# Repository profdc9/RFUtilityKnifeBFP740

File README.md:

This is a pack of RF circuits all laid out onto the same PCB.  They use the X-band transistor BFP740 with 44 GHz transition frequency.  There are five circuits: an Active RF probe, a Active RF Differential Probe, series and shunt noises generator, a Gilbert cell mixer, and a RF amplifier.

These designs are by D. Marks KW4TI and are distributed under the Creative Commons Shared Alike Attribution (CC-BY-SA 4.0) license.

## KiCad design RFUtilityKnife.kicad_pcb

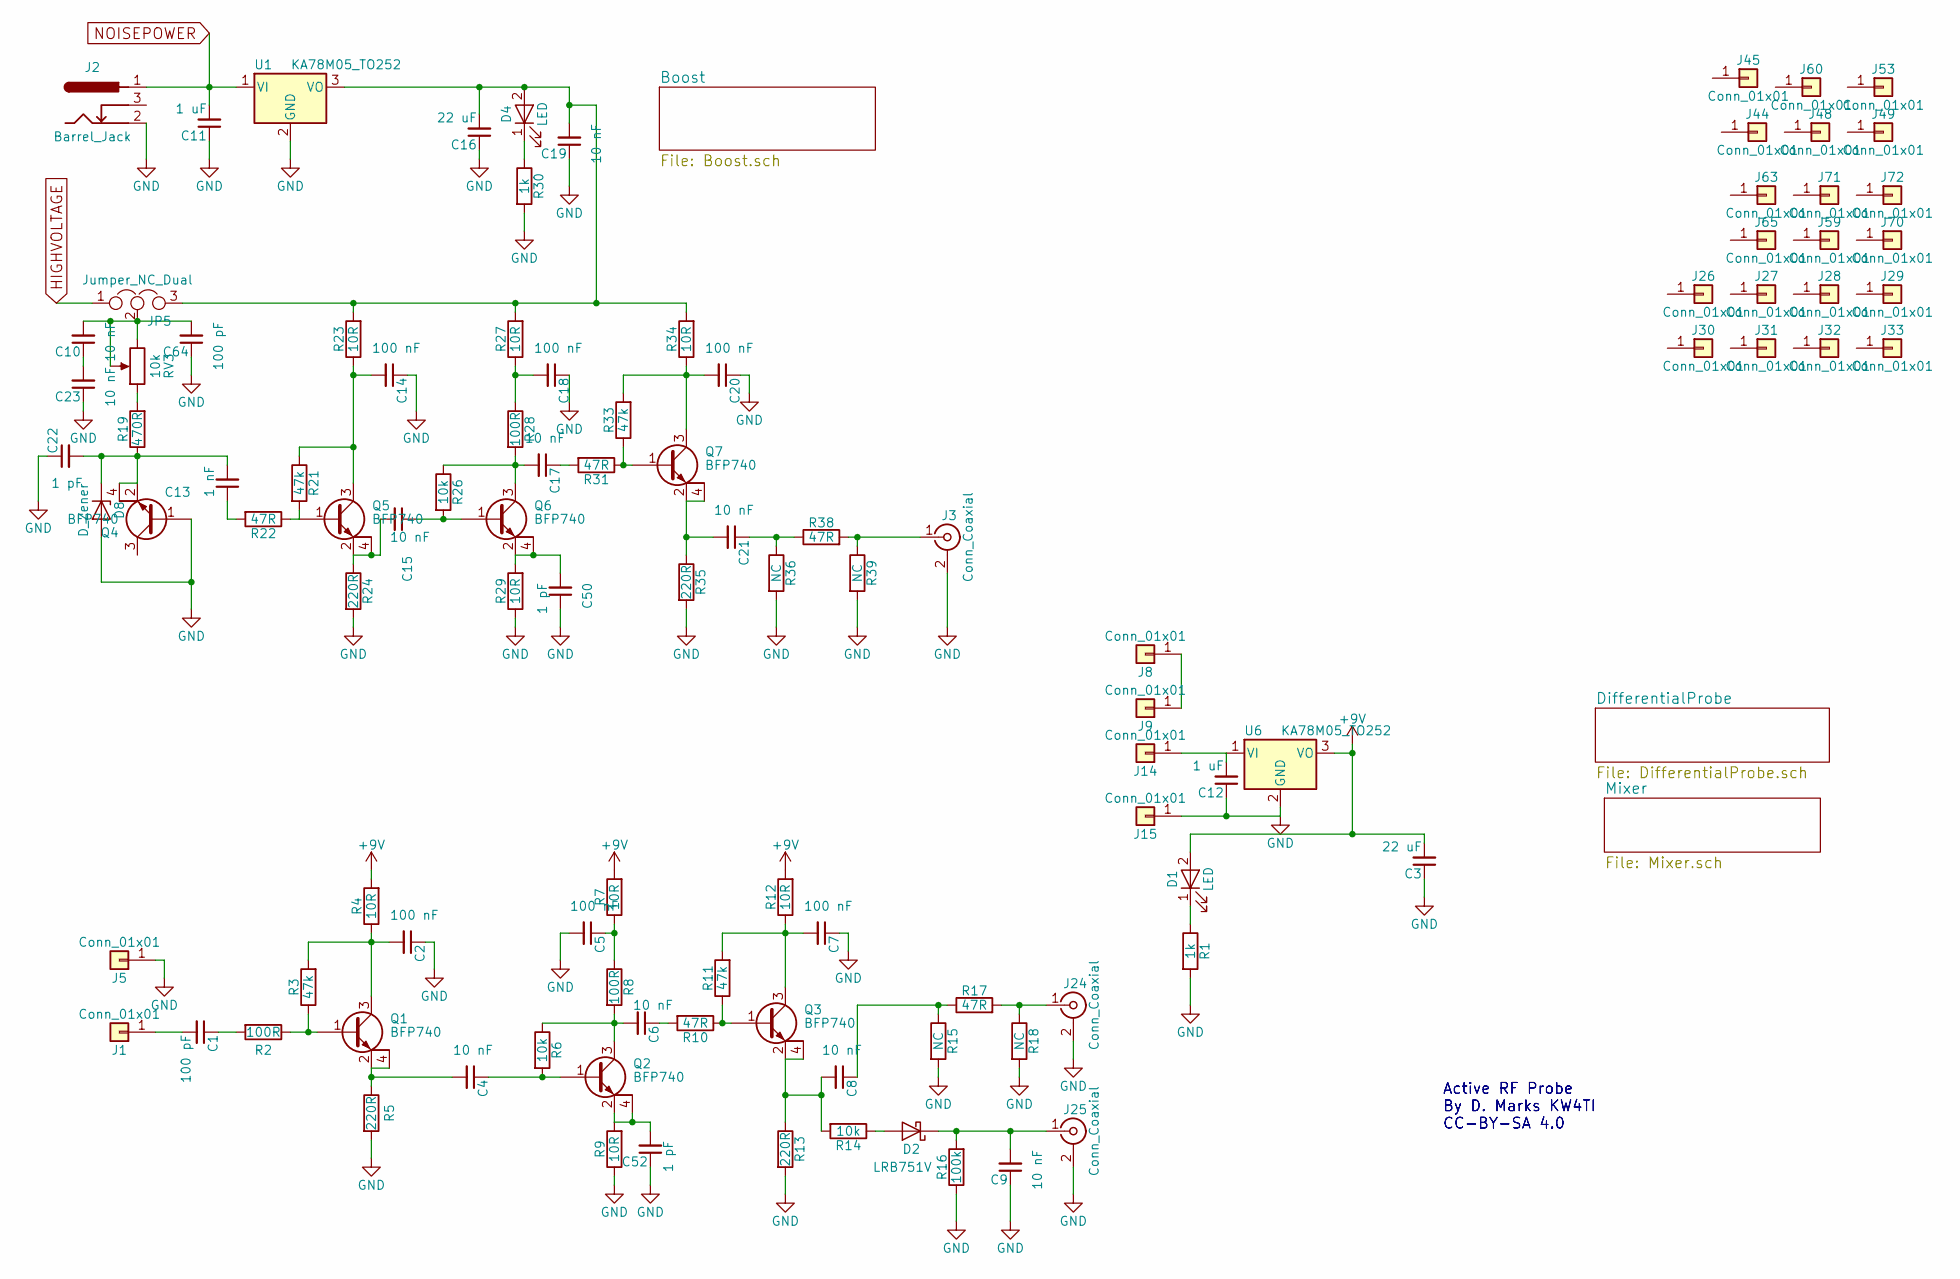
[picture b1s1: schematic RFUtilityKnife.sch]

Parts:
C1: 100 pF; C_0402_NoSilk; LCSC C1546
C2, C5, C7, C14, C18, C20: 100 nF; C_0402_NoSilk; LCSC C1525
C3, C16: 22 uF; C_0805_HandSoldering; LCSC C45783
C4, C6, C8, C15, C17, C21: 10 nF; C_0402_NoSilk; LCSC C15195
C9, C10, C19, C23: 10 nF; C_0805_HandSoldering; LCSC C1710
C11, C12: 1 uF; C_0805_HandSoldering; LCSC C28323
C13: 1 nF; C_0402_NoSilk; LCSC C1523
C22, C50, C52: 1 pF; C_0402_NoSilk; LCSC C14971
C64: 100 pF; C_0805_HandSoldering; LCSC C1790
D1, D4: LED; LED_0805_HandSoldering; LCSC C2296
D2: LRB751V; D_SOD-323_HandSoldering; LCSC C131730
D8: D_Zener; D_MiniMELF
J1, J5, J8, J9, J14, J15: Conn_01x01; PadHole
J2: Barrel_Jack; BARREL_JACK
J3, J24, J25: Conn_Coaxial; Amphenol_RF_SMA_132289
J26, J27, J28, J29, J30, J31, J32, J33, J44, J45, J48, J49, J53, J59, J60, J63, J65, J70, J71, J72: Conn_01x01; BigSlot
JP5: Jumper_NC_Dual; Pin_Header_Straight_1x03_Pitch2.54mm
Q1, Q2, Q3, Q4, Q5, Q6, Q7: BFP740; SOT-343_SC-70-4_Handsoldering
R1, R30: 1k; R_0805_HandSoldering; LCSC C17513
R2, R8, R28: 100R; R_0402_NoSilk; LCSC C25076
R3, R11, R21, R33: 47k; R_0402_NoSilk; LCSC C25792
R4, R7, R9, R12, R23, R27, R29, R34: 10R; R_0402_NoSilk; LCSC C25077
R5, R13, R24, R35: 220R; R_0402_NoSilk; LCSC C25091
R6, R14, R26: 10k; R_0402_NoSilk; LCSC C25744
R10, R17, R22, R31, R38: 47R; R_0402_NoSilk; LCSC C25118
R15, R18, R36, R39: NC; R_0402_NoSilk
R16: 100k; R_0402_NoSilk; LCSC C25741
R19: 470R; R_0402_NoSilk; LCSC C25117
RV3: 10k; Potentiometer_Triwood_RM-065
U1, U6: KA78M05_TO252; TO-252-3_TabPin2; LCSC C58069

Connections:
+9V: C3.2, D1.2 (A), R4.2, R7.2, R12.2, U6.3 (VO)
GND: C2.1, C3.1, C5.2, C7.1, C9.1, C11.1, C12.1, C14.1, C16.1, C18.1, C19.1, C20.1, C22.1, C23.1, C50.1, C52.1, C64.1, D8.2 (A), J2.2, J3.2 (Ext), J5.1, J15.1, J24.2 (Ext), J25.2 (Ext), Q4.1 (B), R1.2, R5.2, R9.1, R13.2, R15.2, R16.1, R18.2, R24.2, R29.1, R30.2, R35.2, R36.2, R39.2, U1.2 (GND), U6.2 (GND); also elsewhere on the board
HIGHVOLTAGE: JP5.1; also elsewhere on the board
NOISEPOWER: C11.2, J2.1, U1.1 (VI); also elsewhere on the board
unnamed: C1.1, R2.2
unnamed: C1.2, J1.1
unnamed: C2.2, Q1.3 (C), R3.2, R4.1
unnamed: C4.1, Q2.1 (B), R6.2
unnamed: C4.2, Q1.2 (E), Q1.4 (E2), R5.1
unnamed: C5.1, R7.1, R8.1
unnamed: C6.1, R10.2
unnamed: C6.2, Q2.3 (C), R6.1, R8.2
unnamed: C7.2, Q3.3 (C), R11.2, R12.1
unnamed: C8.1, R15.1, R17.1
unnamed: C8.2, Q3.2 (E), Q3.4 (E2), R13.1, R14.2
unnamed: C9.2, D2.1 (K), J25.1 (In), R16.2
unnamed: C10.1, C23.2
unnamed: C10.2, C64.2, JP5.2, RV3.2, RV3.3
unnamed: C12.2, J14.1, U6.1 (VI)
unnamed: C13.1, R22.2
unnamed: C13.2, C22.2, D8.1 (K), Q4.2 (E), Q4.4 (E2), R19.1
unnamed: C14.2, Q5.3 (C), R21.1, R23.1
unnamed: C15.1, Q6.1 (B), R26.2
unnamed: C15.2, Q5.2 (E), Q5.4 (E2), R24.1
unnamed: C16.2, C19.2, D4.2 (A), JP5.3, R23.2, R27.2, R34.2, U1.3 (VO)
unnamed: C17.1, R31.2
unnamed: C17.2, Q6.3 (C), R26.1, R28.2
unnamed: C18.2, R27.1, R28.1
unnamed: C20.2, Q7.3 (C), R33.2, R34.1
unnamed: C21.1, R36.1, R38.1
unnamed: C21.2, Q7.2 (E), Q7.4 (E2), R35.1
unnamed: C50.2, Q6.2 (E), Q6.4 (E2), R29.2
unnamed: C52.2, Q2.2 (E), Q2.4 (E2), R9.2
unnamed: D1.1 (K), R1.1
unnamed: D2.2 (A), R14.1
unnamed: D4.1 (K), R30.1
unnamed: J3.1 (In), R38.2, R39.1
unnamed: J8.1, J9.1
unnamed: J24.1 (In), R17.2, R18.1
unnamed: Q1.1 (B), R2.1, R3.1
unnamed: Q3.1 (B), R10.1, R11.1
unnamed: Q5.1 (B), R21.2, R22.1
unnamed: Q7.1 (B), R31.1, R33.1
unnamed: R19.2, RV3.1

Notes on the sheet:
Active RF Probe By D. Marks KW4TI CC-BY-SA 4.0

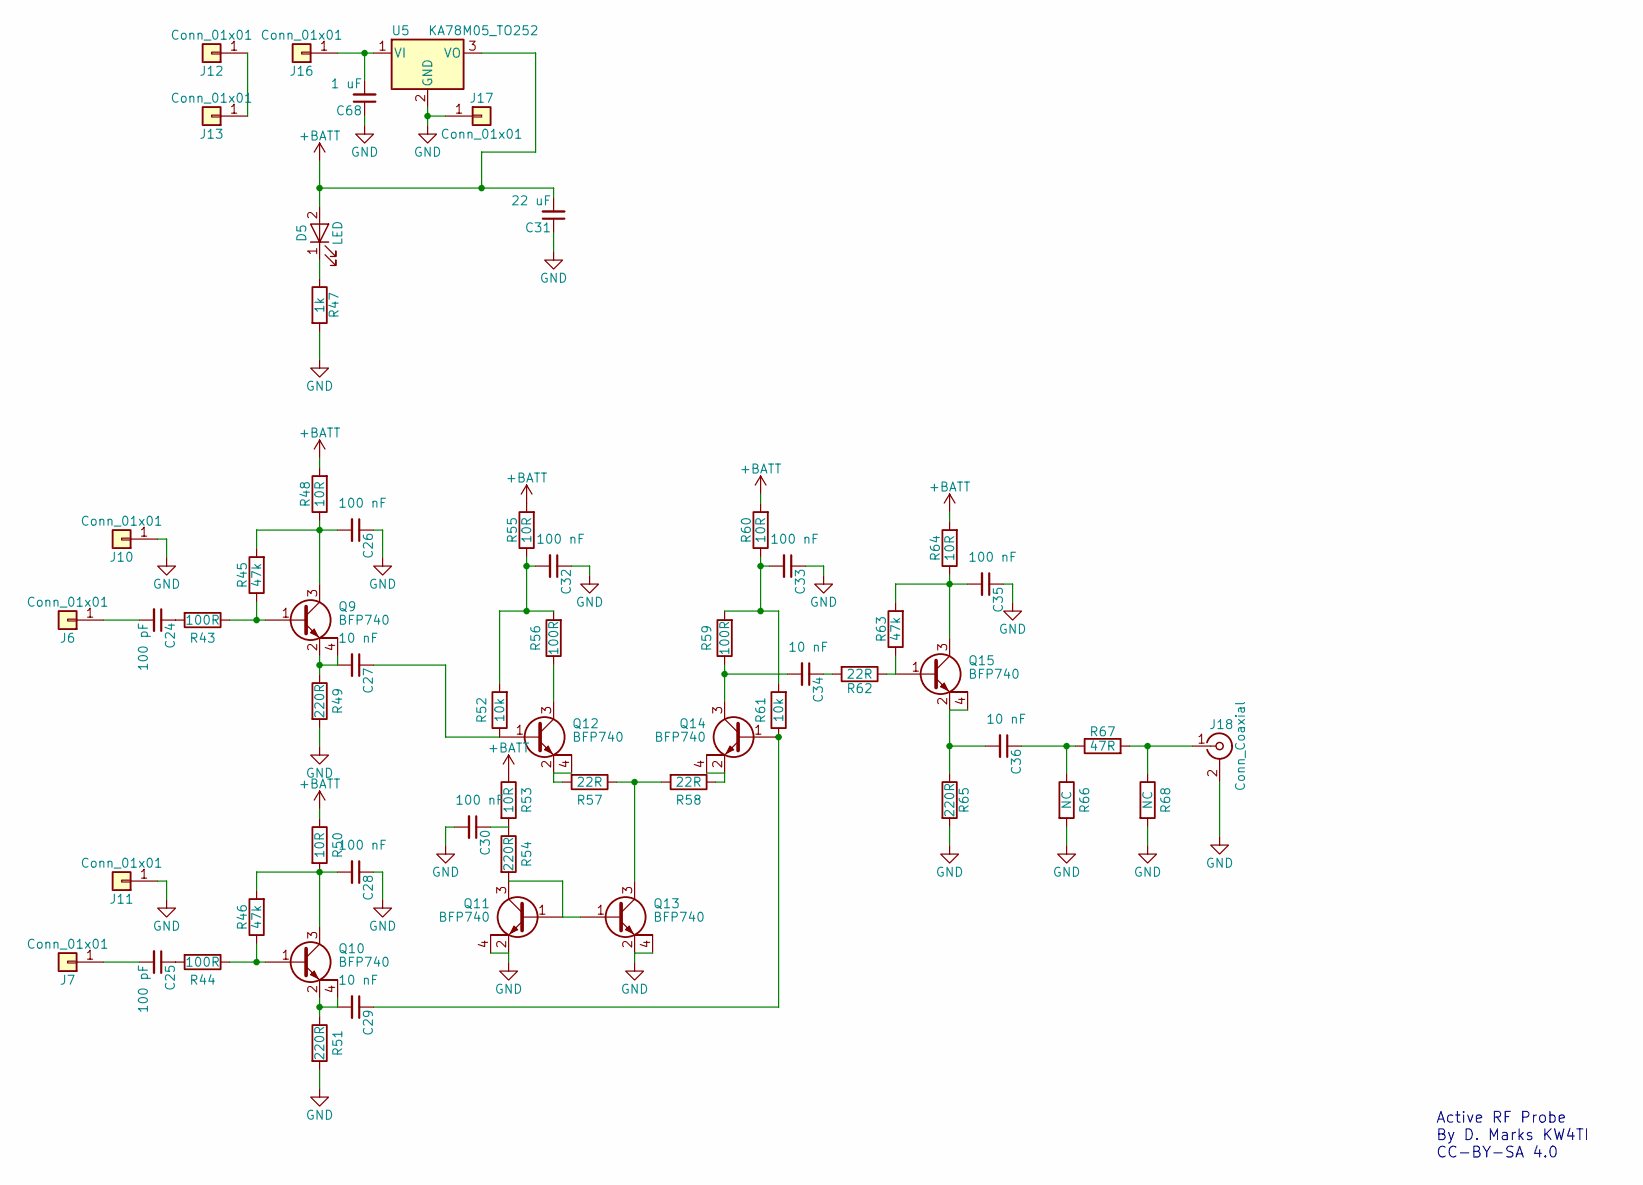
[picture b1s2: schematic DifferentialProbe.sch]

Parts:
C24, C25: 100 pF; C_0402_NoSilk; LCSC C1546
C26, C28, C30, C32, C33, C35: 100 nF; C_0402_NoSilk; LCSC C1525
C27, C29, C34, C36: 10 nF; C_0402_NoSilk; LCSC C15195
C31: 22 uF; C_0805_HandSoldering; LCSC C45783
C68: 1 uF; C_0805_HandSoldering; LCSC C28323
D5: LED; LED_0805_HandSoldering; LCSC C2296
J6, J7, J10, J11, J12, J13, J16, J17: Conn_01x01; PadHole
J18: Conn_Coaxial; Amphenol_RF_SMA_132289
Q9, Q10, Q11, Q12, Q13, Q14, Q15: BFP740; SOT-343_SC-70-4_Handsoldering
R43, R44, R56, R59: 100R; R_0402_NoSilk; LCSC C25076
R45, R46, R63: 47k; R_0402_NoSilk; LCSC C25792
R47: 1k; R_0805_HandSoldering; LCSC C17513
R48, R50, R53, R55, R60, R64: 10R; R_0402_NoSilk; LCSC C25077
R49, R51, R54, R65: 220R; R_0402_NoSilk; LCSC C25091
R52, R61: 10k; R_0402_NoSilk; LCSC C25744
R57, R58, R62: 22R; R_0402_NoSilk; LCSC C25092
R66, R68: NC; R_0402_NoSilk
R67: 47R; R_0402_NoSilk; LCSC C25118
U5: KA78M05_TO252; TO-252-3_TabPin2; LCSC C58069

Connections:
+BATT: C31.2, D5.2 (A), R48.2, R50.1, R53.1, R55.2, R60.2, R64.2, U5.3 (VO)
GND: C26.1, C28.1, C30.2, C31.1, C32.1, C33.1, C35.1, C68.1, J10.1, J11.1, J17.1, J18.2 (Ext), Q11.2 (E), Q11.4 (E2), Q13.2 (E), Q13.4 (E2), R47.2, R49.2, R51.2, R65.2, R66.2, R68.2, U5.2 (GND); also elsewhere on the board
unnamed: C24.1, R43.2
unnamed: C24.2, J6.1
unnamed: C25.1, R44.2
unnamed: C25.2, J7.1
unnamed: C26.2, Q9.3 (C), R45.2, R48.1
unnamed: C27.1, Q12.1 (B), R52.1
unnamed: C27.2, Q9.2 (E), Q9.4 (E2), R49.1
unnamed: C28.2, Q10.3 (C), R46.2, R50.2
unnamed: C29.1, Q14.1 (B), R61.1
unnamed: C29.2, Q10.2 (E), Q10.4 (E2), R51.1
unnamed: C30.1, R53.2, R54.1
unnamed: C32.2, R52.2, R55.1, R56.2
unnamed: C33.2, R59.2, R60.1, R61.2
unnamed: C34.1, R62.2
unnamed: C34.2, Q14.3 (C), R59.1
unnamed: C35.2, Q15.3 (C), R63.2, R64.1
unnamed: C36.1, R66.1, R67.1
unnamed: C36.2, Q15.2 (E), Q15.4 (E2), R65.1
unnamed: C68.2, J16.1, U5.1 (VI)
unnamed: D5.1 (K), R47.1
unnamed: J12.1, J13.1
unnamed: J18.1 (In), R67.2, R68.1
unnamed: Q9.1 (B), R43.1, R45.1
unnamed: Q10.1 (B), R44.1, R46.1
unnamed: Q11.1 (B), Q11.3 (C), Q13.1 (B), R54.2
unnamed: Q12.2 (E), Q12.4 (E2), R57.2
unnamed: Q12.3 (C), R56.1
unnamed: Q13.3 (C), R57.1, R58.2
unnamed: Q14.2 (E), Q14.4 (E2), R58.1
unnamed: Q15.1 (B), R62.1, R63.1

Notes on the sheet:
Active RF Probe By D. Marks KW4TI CC-BY-SA 4.0

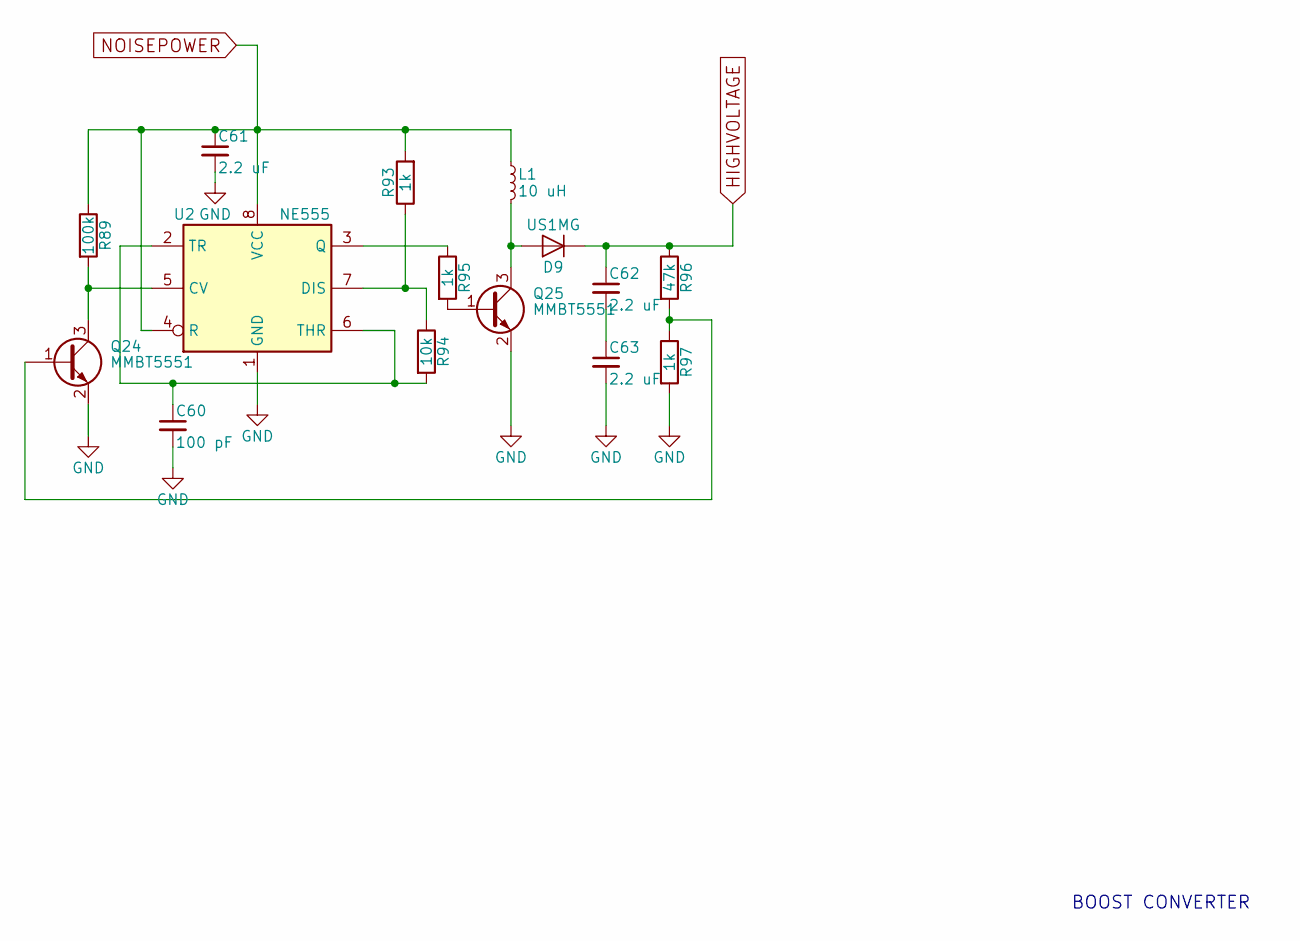
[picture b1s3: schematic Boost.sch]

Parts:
C60: 100 pF; C_0805_HandSoldering; LCSC C1790
C61, C62, C63: 2.2 uF; C_0805_HandSoldering; LCSC C49217
D9: US1MG; D_SMA_Handsoldering; LCSC C412437
L1: 10 uH; L_7.3x7.3_H4.5
Q24, Q25: MMBT5551; SOT-23; LCSC C2145
R89: 100k; R_0805_HandSoldering; LCSC C17407
R93, R95, R97: 1k; R_0805_HandSoldering; LCSC C17513
R94: 10k; R_0805_HandSoldering; LCSC C17414
R96: 47k; R_0805_HandSoldering; LCSC C17713
U2: NE555; SOIC-8_3.9x4.9mm_Pitch1.27mm; LCSC C7593

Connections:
GND: C60.2, C61.2, C63.2, Q24.2 (E), Q25.2 (E), R97.2, U2.1 (GND); also elsewhere on the board
HIGHVOLTAGE: C62.1, D9.1 (K), R96.1; also elsewhere on the board
NOISEPOWER: C61.1, L1.1, R89.1, R93.2, U2.4 (R), U2.8 (VCC); also elsewhere on the board
unnamed: C60.1, R94.2, U2.2 (TR), U2.6 (THR)
unnamed: C62.2, C63.1
unnamed: D9.2 (A), L1.2, Q25.3 (C)
unnamed: Q24.1 (B), R96.2, R97.1
unnamed: Q24.3 (C), R89.2, U2.5 (CV)
unnamed: Q25.1 (B), R95.2
unnamed: R93.1, R94.1, U2.7 (DIS)
unnamed: R95.1, U2.3 (Q)

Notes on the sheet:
BOOST CONVERTER

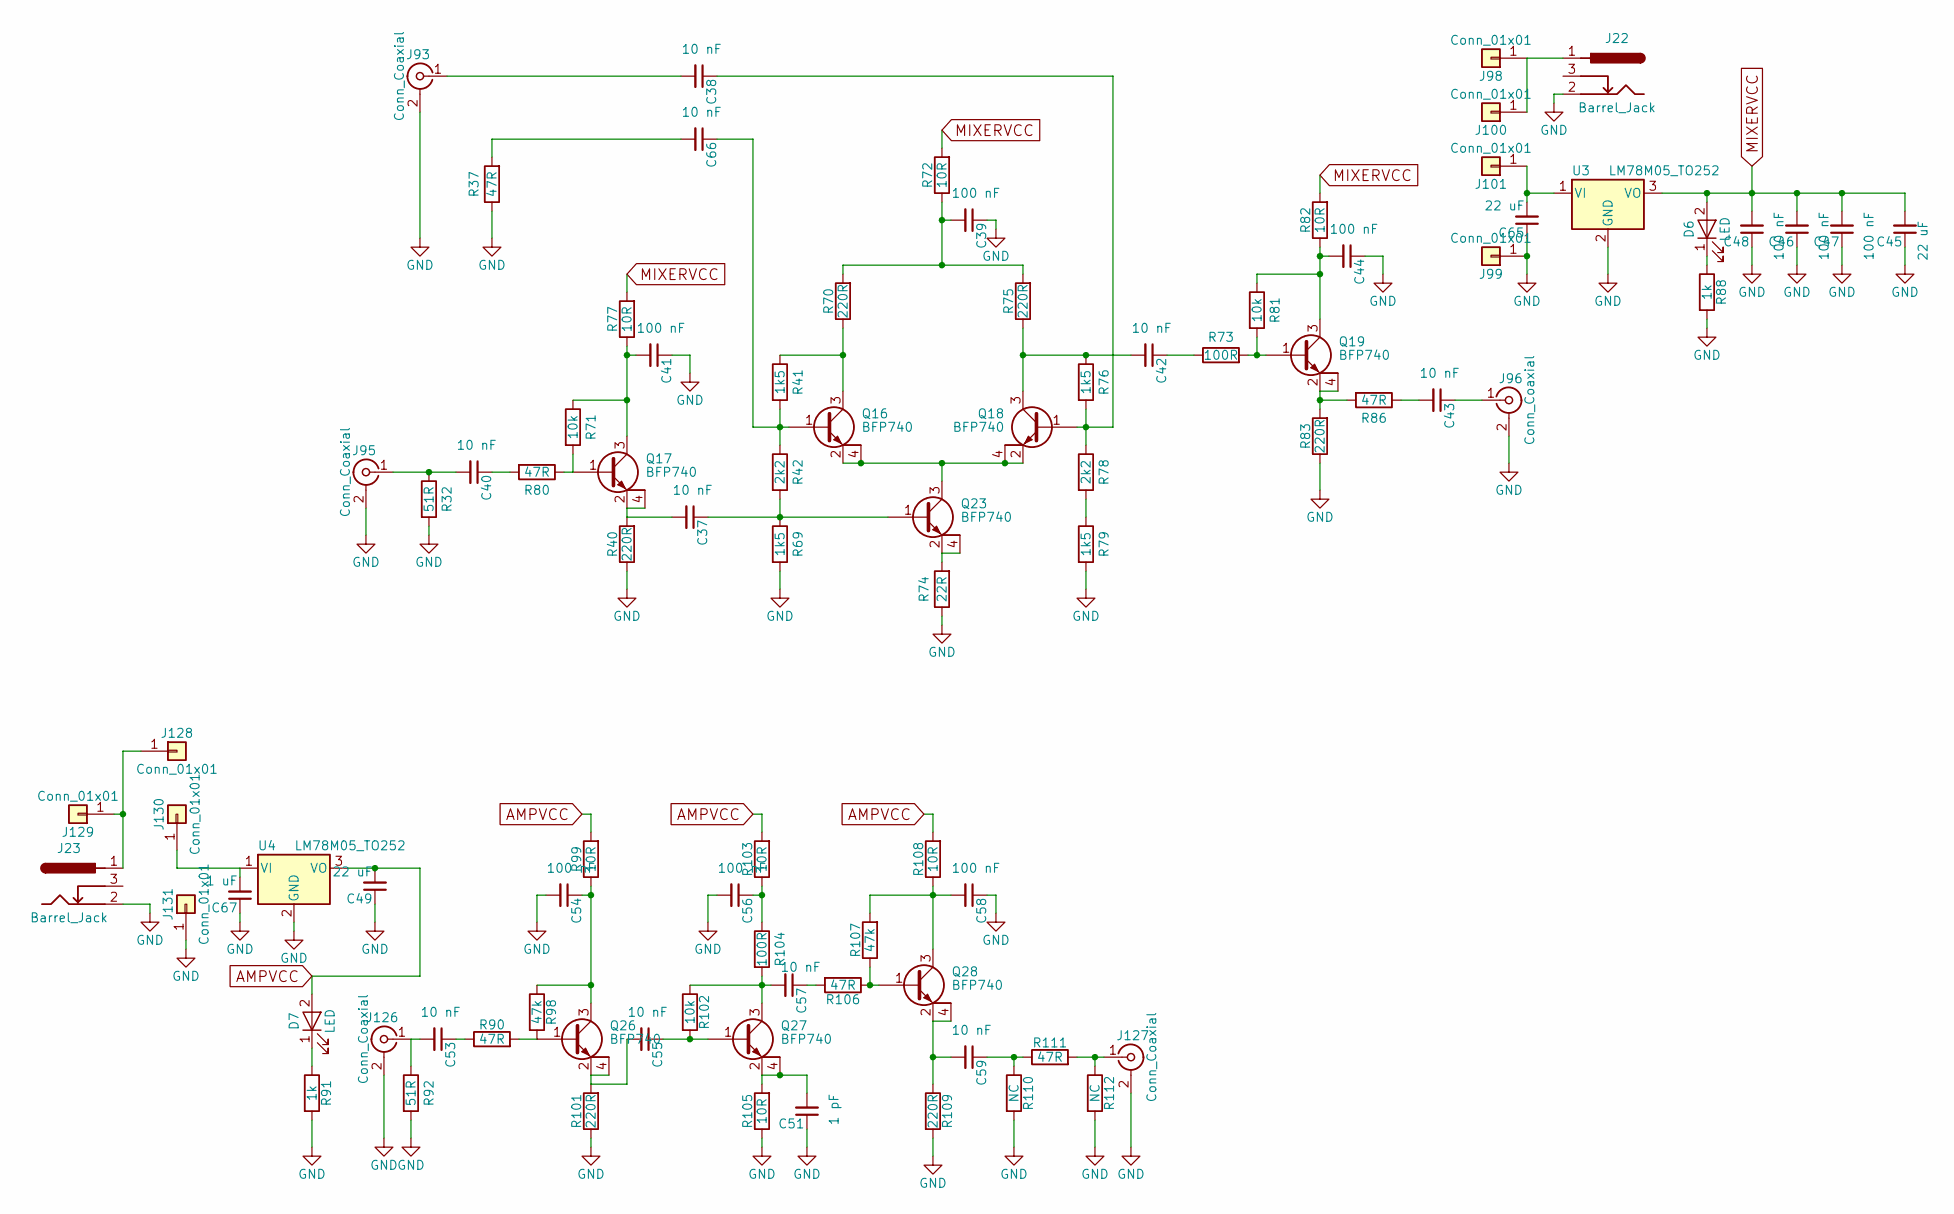
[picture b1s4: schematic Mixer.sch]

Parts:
C37, C38, C40, C42, C43, C53, C55, C57, C59, C66: 10 nF; C_0402_NoSilk; LCSC C15195
C39, C41, C44, C54, C56, C58: 100 nF; C_0402_NoSilk; LCSC C1525
C45, C49, C65: 22 uF; C_0805_HandSoldering; LCSC C45783
C46, C47, C48: 100 nF; C_0805_HandSoldering; LCSC C49678
C51: 1 pF; C_0402_NoSilk; LCSC C14971
C67: 1 uF; C_0805_HandSoldering; LCSC C28323
D6, D7: LED; LED_0805_HandSoldering; LCSC C2296
J22, J23: Barrel_Jack; BARREL_JACK
J93, J95, J96, J126, J127: Conn_Coaxial; Amphenol_RF_SMA_132289
J98, J99, J100, J101, J128, J129, J130, J131: Conn_01x01; PadHole
Q16, Q17, Q18, Q19, Q23, Q26, Q27, Q28: BFP740; SOT-343_SC-70-4_Handsoldering
R32, R92: 51R; R_0402_NoSilk; LCSC C25125
R37, R80, R86, R90, R106, R111: 47R; R_0402_NoSilk; LCSC C25118
R40, R70, R75, R83, R101, R109: 220R; R_0402_NoSilk; LCSC C25091
R41, R69, R76, R79: 1k5; R_0402_NoSilk; LCSC C25867
R42, R78: 2k2; R_0402_NoSilk; LCSC C25879
R71, R81, R102: 10k; R_0402_NoSilk; LCSC C25744
R72, R77, R82, R99, R103, R105, R108: 10R; R_0402_NoSilk; LCSC C25077
R73, R104: 100R; R_0402_NoSilk; LCSC C25076
R74: 22R; R_0402_NoSilk; LCSC C25092
R88, R91: 1k; R_0805_HandSoldering; LCSC C17513
R98, R107: 47k; R_0402_NoSilk; LCSC C25792
R110, R112: NC; R_0402_NoSilk
U3, U4: LM78M05_TO252; TO-252-3_TabPin2; LCSC C58069

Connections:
AMPVCC: C49.2, D7.2 (A), R99.2, R103.2, R108.2, U4.3 (VO)
GND: C39.1, C41.1, C44.1, C45.1, C46.1, C47.1, C48.1, C49.1, C51.1, C54.2, C56.2, C58.1, C65.1, C67.1, J22.2, J23.2, J93.2 (Ext), J95.2 (Ext), J96.2 (Ext), J99.1, J126.2 (Ext), J127.2 (Ext), J131.1, R32.2, R37.1, R40.1, R69.2, R74.1, R79.2, R83.1, R88.2, R91.2, R92.2, R101.1, R105.1, R109.2, R110.2, R112.2, U3.2 (GND), U4.2 (GND); also elsewhere on the board
MIXERVCC: C45.2, C46.2, C47.2, C48.2, D6.2 (A), R72.2, R77.2, R82.2, U3.3 (VO)
unnamed: C37.1, Q23.1 (B), R42.2, R69.1
unnamed: C37.2, Q17.2 (E), Q17.4 (E2), R40.2
unnamed: C38.1, Q18.1 (B), R76.2, R78.1
unnamed: C38.2, J93.1 (In)
unnamed: C39.2, R70.2, R72.1, R75.2
unnamed: C40.1, R80.2
unnamed: C40.2, J95.1 (In), R32.1
unnamed: C41.2, Q17.3 (C), R71.1, R77.1
unnamed: C42.1, R73.1
unnamed: C42.2, Q18.3 (C), R75.1, R76.1
unnamed: C43.1, J96.1 (In)
unnamed: C43.2, R86.1
unnamed: C44.2, Q19.3 (C), R81.1, R82.1
unnamed: C51.2, Q27.2 (E), Q27.4 (E2), R105.2
unnamed: C53.1, R90.1
unnamed: C53.2, J126.1 (In), R92.1
unnamed: C54.1, Q26.3 (C), R98.1, R99.1
unnamed: C55.1, Q27.1 (B), R102.2
unnamed: C55.2, Q26.2 (E), Q26.4 (E2), R101.2
unnamed: C56.1, R103.1, R104.1
unnamed: C57.1, R106.2
unnamed: C57.2, Q27.3 (C), R102.1, R104.2
unnamed: C58.2, Q28.3 (C), R107.2, R108.1
unnamed: C59.1, R110.1, R111.1
unnamed: C59.2, Q28.2 (E), Q28.4 (E2), R109.1
unnamed: C65.2, J101.1, U3.1 (VI)
unnamed: C66.1, Q16.1 (B), R41.2, R42.1
unnamed: C66.2, R37.2
unnamed: C67.2, J130.1, U4.1 (VI)
unnamed: D6.1 (K), R88.1
unnamed: D7.1 (K), R91.1
unnamed: J22.1, J98.1, J100.1
unnamed: J127.1 (In), R111.2, R112.1
unnamed: J23.1, J128.1, J129.1
unnamed: Q16.2 (E), Q16.4 (E2), Q18.2 (E), Q18.4 (E2), Q23.3 (C)
unnamed: Q16.3 (C), R41.1, R70.1
unnamed: Q17.1 (B), R71.2, R80.1
unnamed: Q19.1 (B), R73.2, R81.2
unnamed: Q19.2 (E), Q19.4 (E2), R83.2, R86.2
unnamed: Q23.2 (E), Q23.4 (E2), R74.2
unnamed: Q26.1 (B), R90.2, R98.2
unnamed: Q28.1 (B), R106.1, R107.1
unnamed: R78.2, R79.1

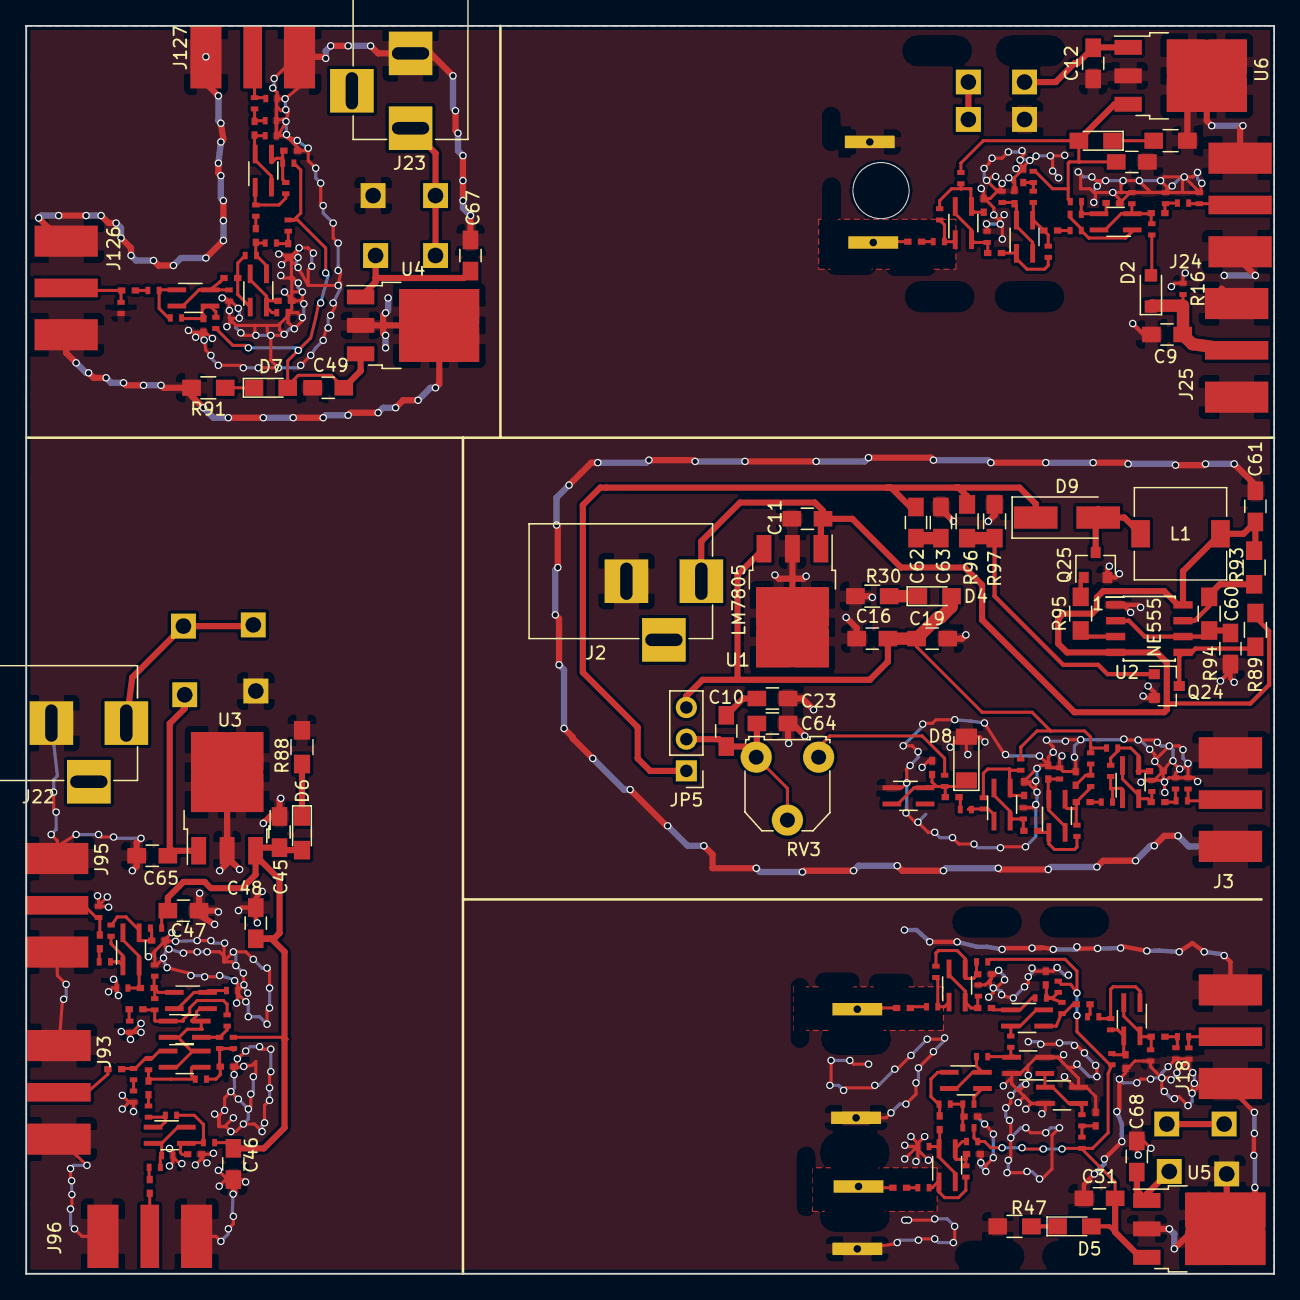
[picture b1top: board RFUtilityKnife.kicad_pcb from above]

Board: 2 copper layers, 100.0 x 100.0 mm, 269 parts (0 on the bottom side), 128 nets.

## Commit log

2020-07-13 Forgot to update picture
2020-07-13 Updated gerber
2020-07-17 Cleaned up the layout
2020-07-31 Added vias and changed cut lines
